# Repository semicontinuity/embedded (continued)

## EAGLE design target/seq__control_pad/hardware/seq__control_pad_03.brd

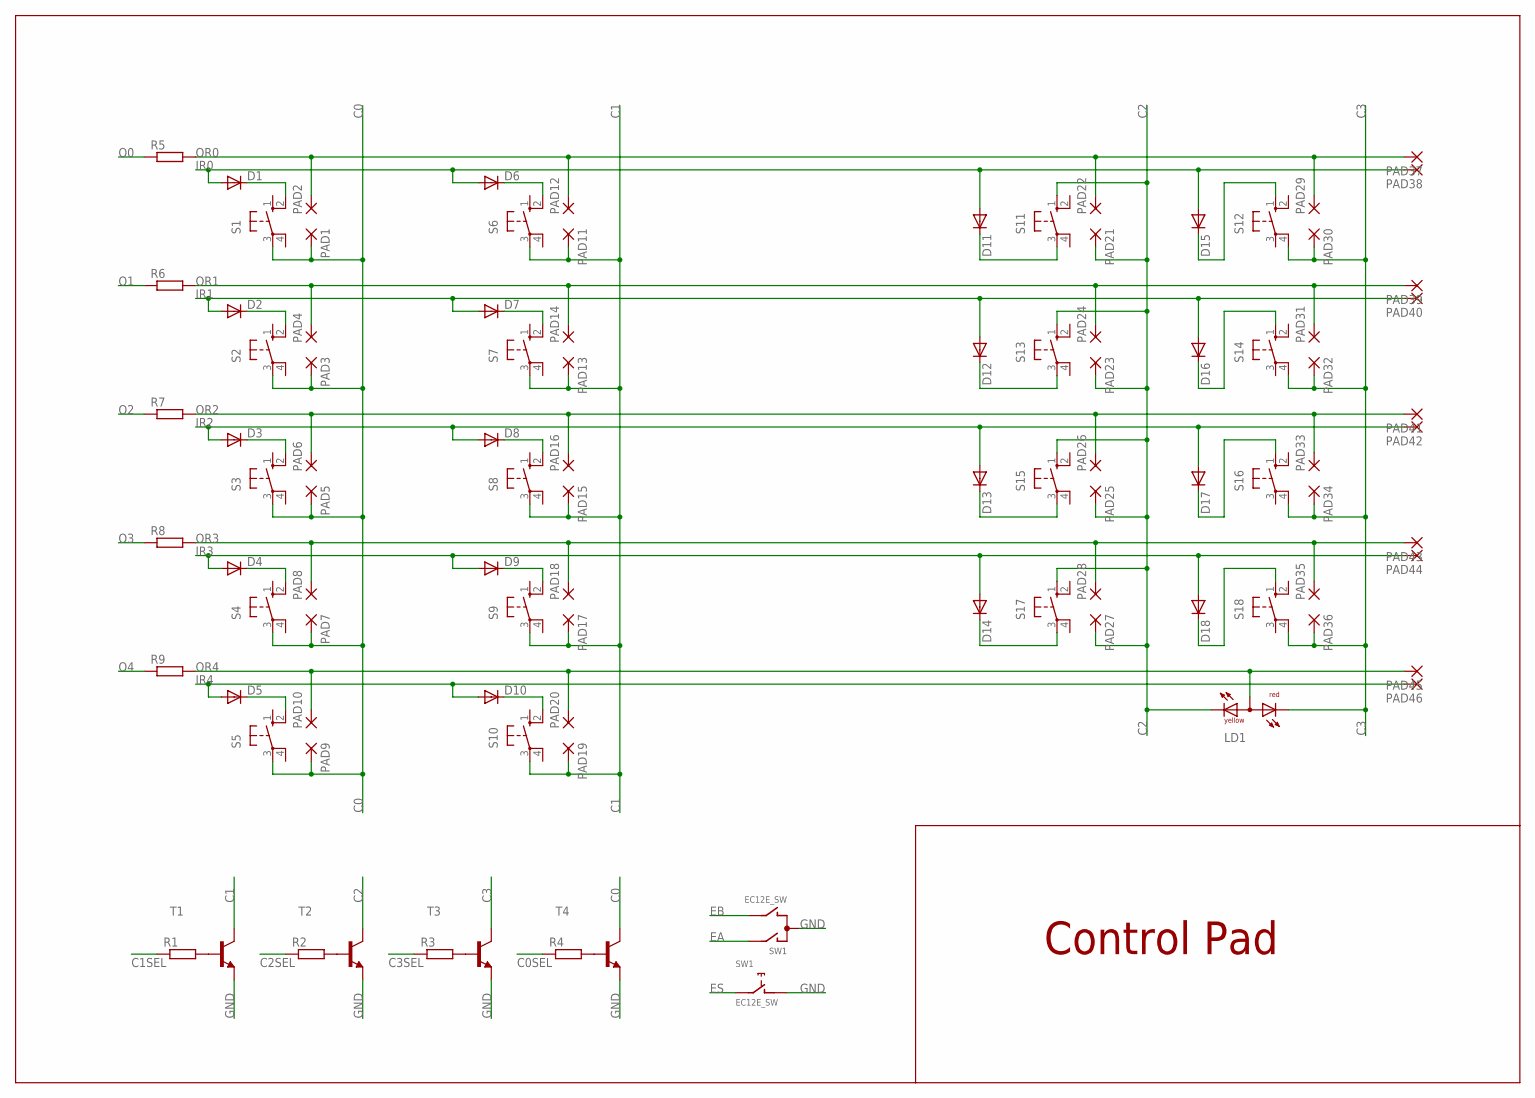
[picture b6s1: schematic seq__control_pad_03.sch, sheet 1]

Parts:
D1, D2, D3, D4, D5, D6, D7, D8, D9, D10, D11, D12, D13, D14, D15, D16, D17, D18: DIODE-MINIMELF; MINIMELF
LD1: DUOLED-RY-A; DUOLED-A-5MM
PAD1, PAD2, PAD3, PAD4, PAD5, PAD6, PAD7, PAD8, PAD9, PAD10, PAD11, PAD12, PAD13, PAD14, PAD15, PAD16, PAD17, PAD18, PAD19, PAD20, PAD21, PAD22, PAD23, PAD24, PAD25, PAD26, PAD27, PAD28, PAD29, PAD30, PAD31, PAD32, PAD33, PAD34, PAD35, PAD36, PAD37, PAD38, PAD39, PAD40, PAD41, PAD42, PAD43, PAD44, PAD45, PAD46: 1,6/0,8
R1, R2, R3, R4, R5, R6, R7, R8, R9: R-EU_R0805; R0805
S1, S2, S3, S4, S5, S6, S7, S8, S9, S10, S11, S12, S13, S14, S15, S16, S17, S18: 40-XX; B3F-40XX
SW1: EC12E_SW; ALPS_EC12E_SW
T1, T2, T3, T4: MMBT3904LT1-NPN-SOT23-BEC; SOT23-BEC

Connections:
C0: PAD1.1, PAD3.1, PAD5.1, PAD7.1, PAD9.1, S1.3, S2.3, S3.3, S4.3, S5.3, T4.C
C0SEL: R4.1; also elsewhere on the board
C1: PAD11.1, PAD13.1, PAD15.1, PAD17.1, PAD19.1, S6.3, S7.3, S8.3, S9.3, S10.3, T1.C
C1SEL: R1.1; also elsewhere on the board
C2: LD1.CX (CY), PAD21.1, PAD23.1, PAD25.1, PAD27.1, S11.1 (S), S13.1 (S), S15.1 (S), S17.1 (S), T2.C
C2SEL: R2.1; also elsewhere on the board
C3: LD1.CR, PAD30.1, PAD32.1, PAD34.1, PAD36.1, S12.4 (P1), S14.4 (P1), S16.4 (P1), S18.4 (P1), T3.C
C3SEL: R3.1; also elsewhere on the board
EA: SW1.A; also elsewhere on the board
EB: SW1.B; also elsewhere on the board
ES: SW1.E (2); also elsewhere on the board
GND: SW1.C, SW1.D (1), T1.E, T2.E, T3.E, T4.E; also elsewhere on the board
IR0: D1.A, D6.A, D11.A, D15.A, PAD38.1; also elsewhere on the board
IR1: D2.A, D7.A, D12.A, D16.A, PAD40.1; also elsewhere on the board
IR2: D3.A, D8.A, D13.A, D17.A, PAD42.1; also elsewhere on the board
IR3: D4.A, D9.A, D14.A, D18.A, PAD44.1; also elsewhere on the board
IR4: D5.A, D10.A, PAD46.1; also elsewhere on the board
unnamed: D11.C, S11.3
unnamed: R1.2, T1.B
unnamed: R2.2, T2.B
unnamed: R3.2, T3.B
unnamed: D3.C, S3.2 (S1)
unnamed: D16.C, S14.1 (S)
unnamed: R4.2, T4.B
unnamed: D17.C, S16.1 (S)
unnamed: D18.C, S18.1 (S)
unnamed: D1.C, S1.2 (S1)
unnamed: D2.C, S2.2 (S1)
unnamed: D5.C, S5.2 (S1)
unnamed: D4.C, S4.2 (S1)
unnamed: D6.C, S6.2 (S1)
unnamed: D7.C, S7.2 (S1)
unnamed: D8.C, S8.2 (S1)
unnamed: D9.C, S9.2 (S1)
unnamed: D10.C, S10.2 (S1)
unnamed: D12.C, S13.3
unnamed: D13.C, S15.3
unnamed: D14.C, S17.3
unnamed: D15.C, S12.1 (S)
O0: R5.1; also elsewhere on the board
O1: R6.1; also elsewhere on the board
O2: R7.1; also elsewhere on the board
O3: R8.1; also elsewhere on the board
O4: R9.1; also elsewhere on the board
OR0: PAD2.1, PAD12.1, PAD22.1, PAD29.1, PAD37.1, R5.2
OR1: PAD4.1, PAD14.1, PAD24.1, PAD31.1, PAD39.1, R6.2
OR2: PAD6.1, PAD16.1, PAD26.1, PAD33.1, PAD41.1, R7.2
OR3: PAD8.1, PAD18.1, PAD28.1, PAD35.1, PAD43.1, R8.2
OR4: LD1.A, PAD10.1, PAD20.1, PAD45.1, R9.2

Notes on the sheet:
Control Pad

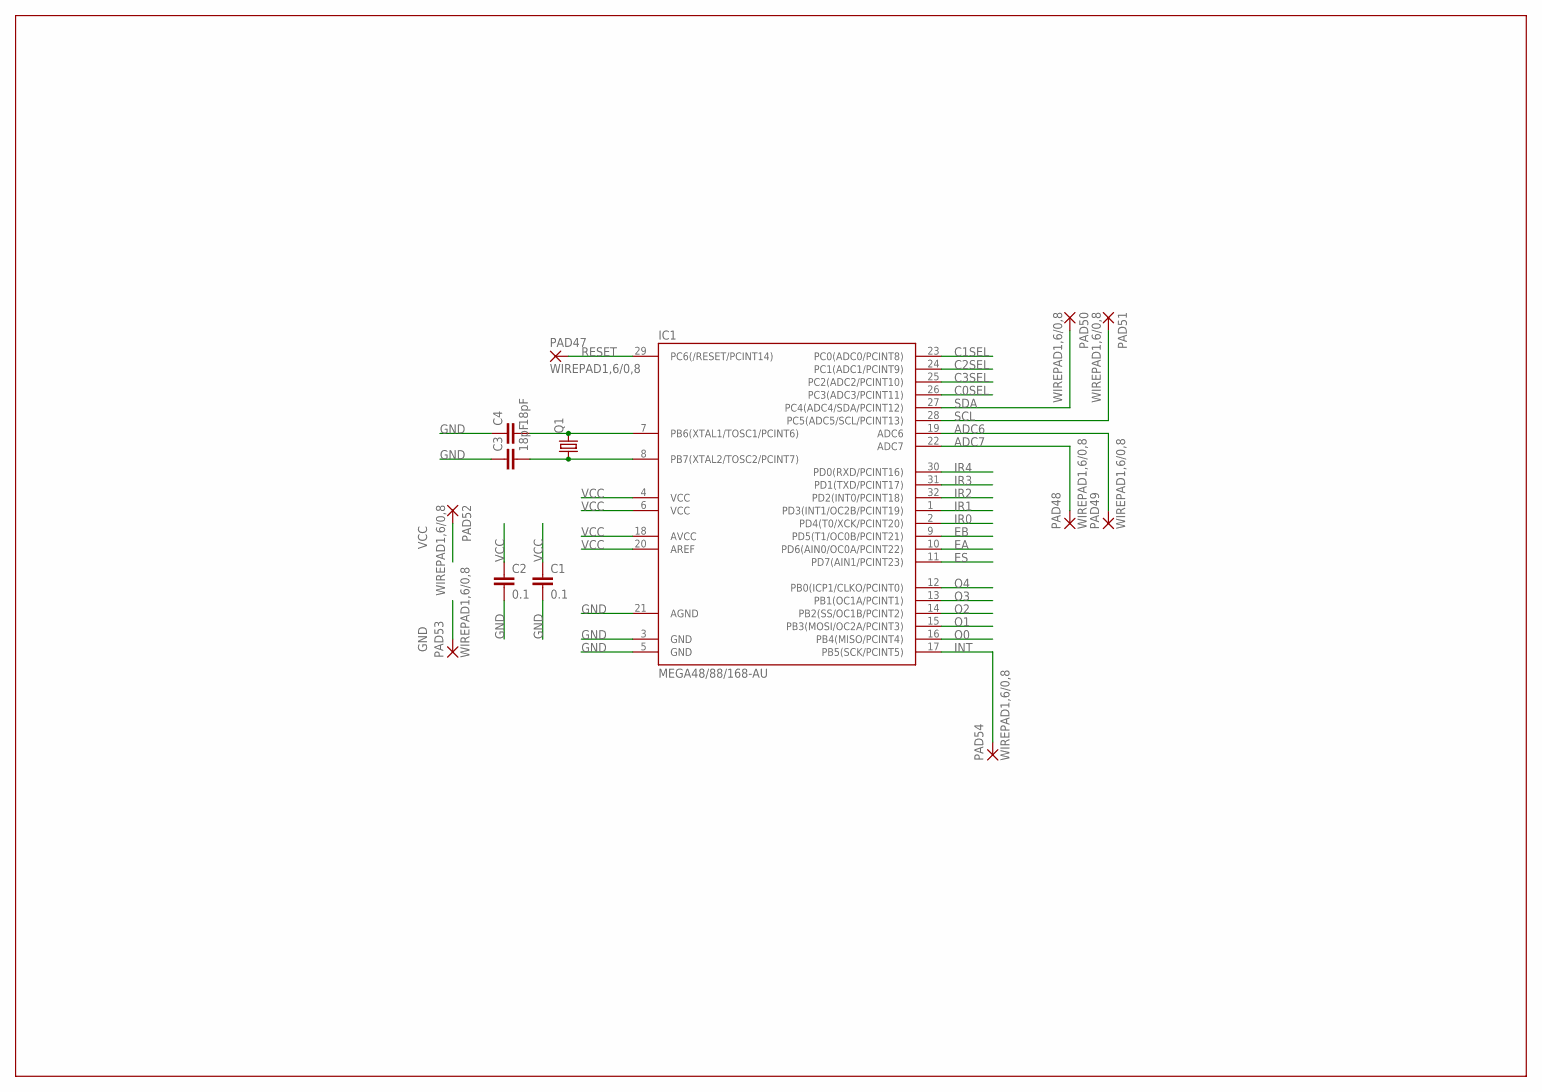
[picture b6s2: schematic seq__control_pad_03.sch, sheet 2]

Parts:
C1, C2: 0.1; C0805
C3, C4: 18pF; C0805
IC1: MEGA48/88/168-AU; TQFP32-08
PAD47, PAD48, PAD49, PAD50, PAD51, PAD52, PAD53, PAD54: WIREPAD1,6/0,8; 1,6/0,8
Q1: CRYSTALHC49S; HC49/S

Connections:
ADC6: IC1.19 (ADC6), PAD49.1
ADC7: IC1.22 (ADC7), PAD48.1
C0SEL: IC1.26 (PC3(ADC3/PCINT11)); also elsewhere on the board
C1SEL: IC1.23 (PC0(ADC0/PCINT8)); also elsewhere on the board
C2SEL: IC1.24 (PC1(ADC1/PCINT9)); also elsewhere on the board
C3SEL: IC1.25 (PC2(ADC2/PCINT10)); also elsewhere on the board
EA: IC1.10 (PD6(AIN0/OC0A/PCINT22)); also elsewhere on the board
EB: IC1.9 (PD5(T1/OC0B/PCINT21)); also elsewhere on the board
ES: IC1.11 (PD7(AIN1/PCINT23)); also elsewhere on the board
GND: C1.2, C2.2, C3.1, C4.1, IC1.3 (GND), IC1.5 (GND), IC1.21 (AGND), PAD53.1; also elsewhere on the board
INT: IC1.17 (PB5(SCK/PCINT5)), PAD54.1
IR0: IC1.2 (PD4(T0/XCK/PCINT20)); also elsewhere on the board
IR1: IC1.1 (PD3(INT1/OC2B/PCINT19)); also elsewhere on the board
IR2: IC1.32 (PD2(INT0/PCINT18)); also elsewhere on the board
IR3: IC1.31 (PD1(TXD/PCINT17)); also elsewhere on the board
IR4: IC1.30 (PD0(RXD/PCINT16)); also elsewhere on the board
O0: IC1.16 (PB4(MISO/PCINT4)); also elsewhere on the board
O1: IC1.15 (PB3(MOSI/OC2A/PCINT3)); also elsewhere on the board
O2: IC1.14 (PB2(SS/OC1B/PCINT2)); also elsewhere on the board
O3: IC1.13 (PB1(OC1A/PCINT1)); also elsewhere on the board
O4: IC1.12 (PB0(ICP1/CLKO/PCINT0)); also elsewhere on the board
RESET: IC1.29 (PC6(/RESET/PCINT14)), PAD47.1
SCL: IC1.28 (PC5(ADC5/SCL/PCINT13)), PAD51.1
SDA: IC1.27 (PC4(ADC4/SDA/PCINT12)), PAD50.1
VCC: C1.1, C2.1, IC1.4 (VCC), IC1.6 (VCC), IC1.18 (AVCC), IC1.20 (AREF), PAD52.1
XTAL1: C4.2, IC1.7 (PB6(XTAL1/TOSC1/PCINT6)), Q1.2
XTAL2: C3.2, IC1.8 (PB7(XTAL2/TOSC2/PCINT7)), Q1.1

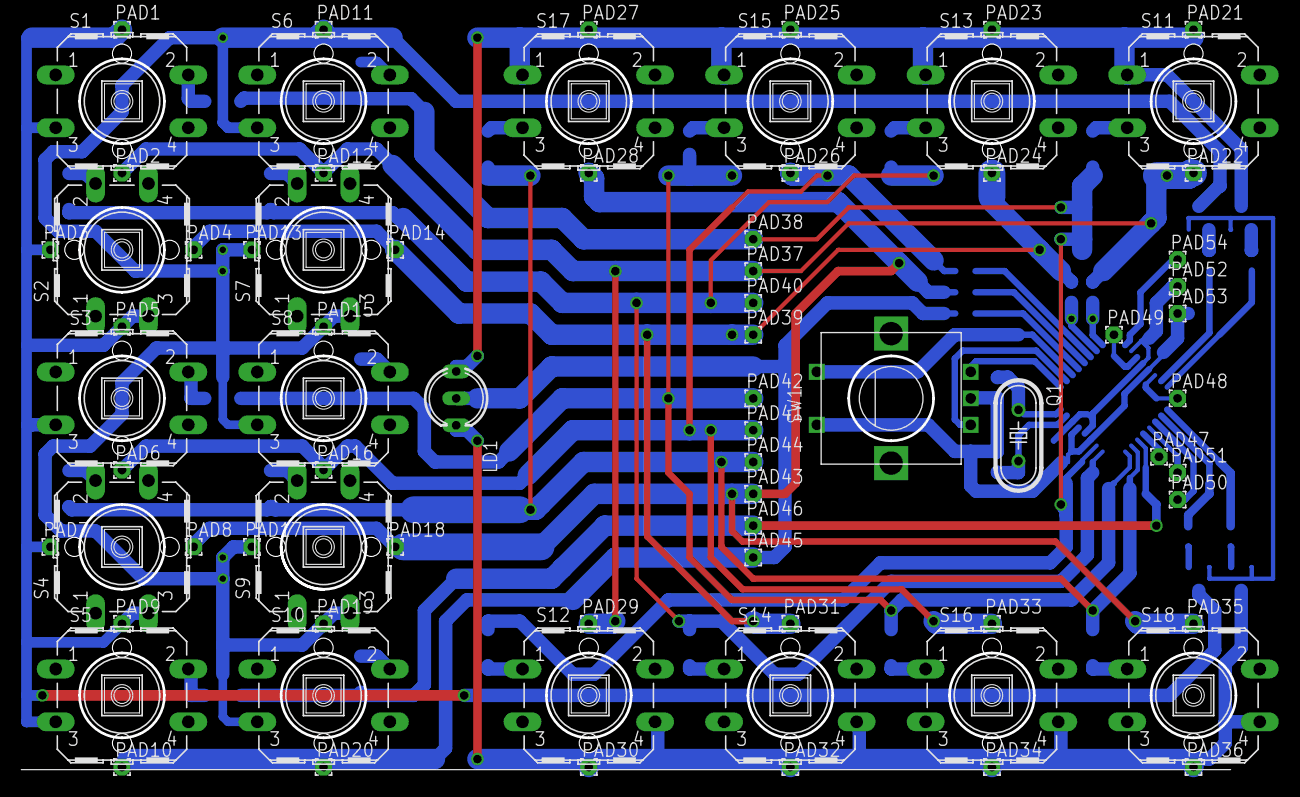
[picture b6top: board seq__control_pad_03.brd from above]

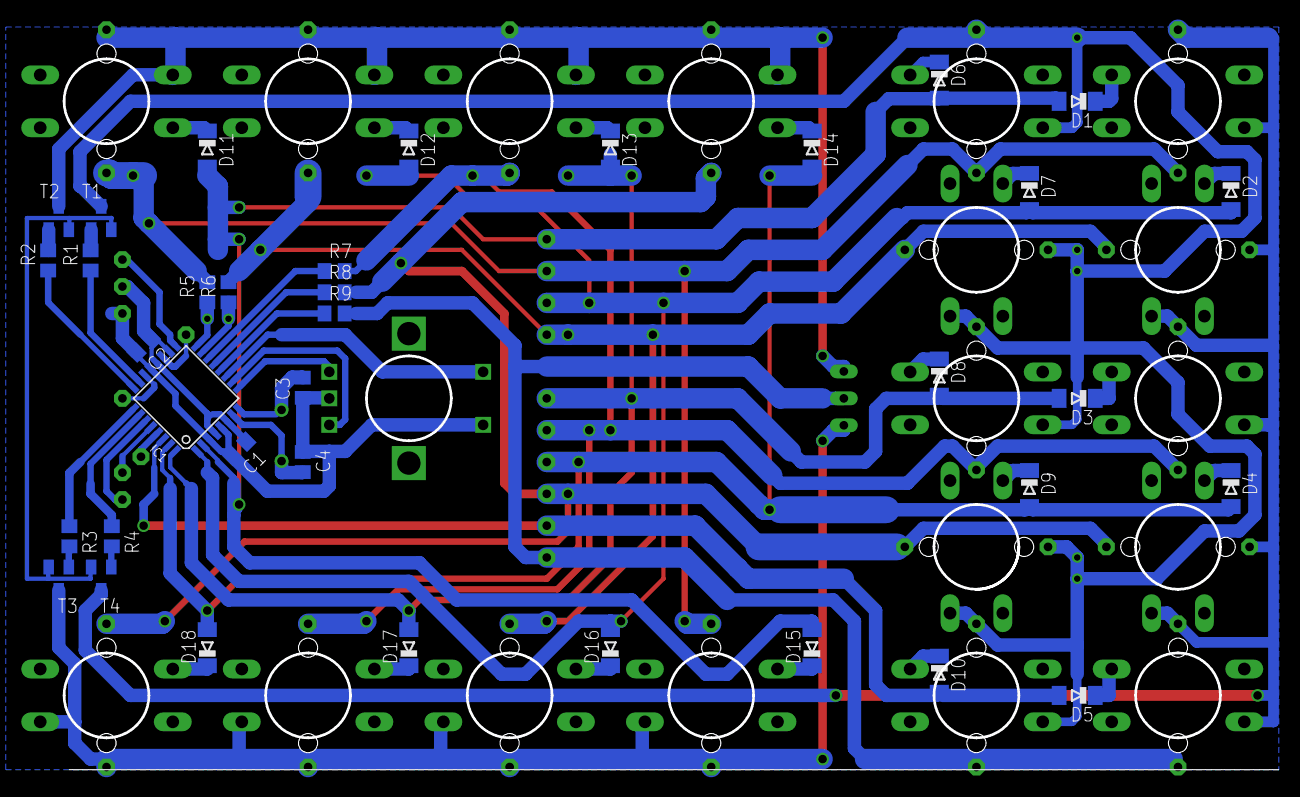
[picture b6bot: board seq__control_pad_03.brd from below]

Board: 2 copper layers, 114.5 x 67.0 mm, 111 parts (36 on the bottom side), 58 nets.

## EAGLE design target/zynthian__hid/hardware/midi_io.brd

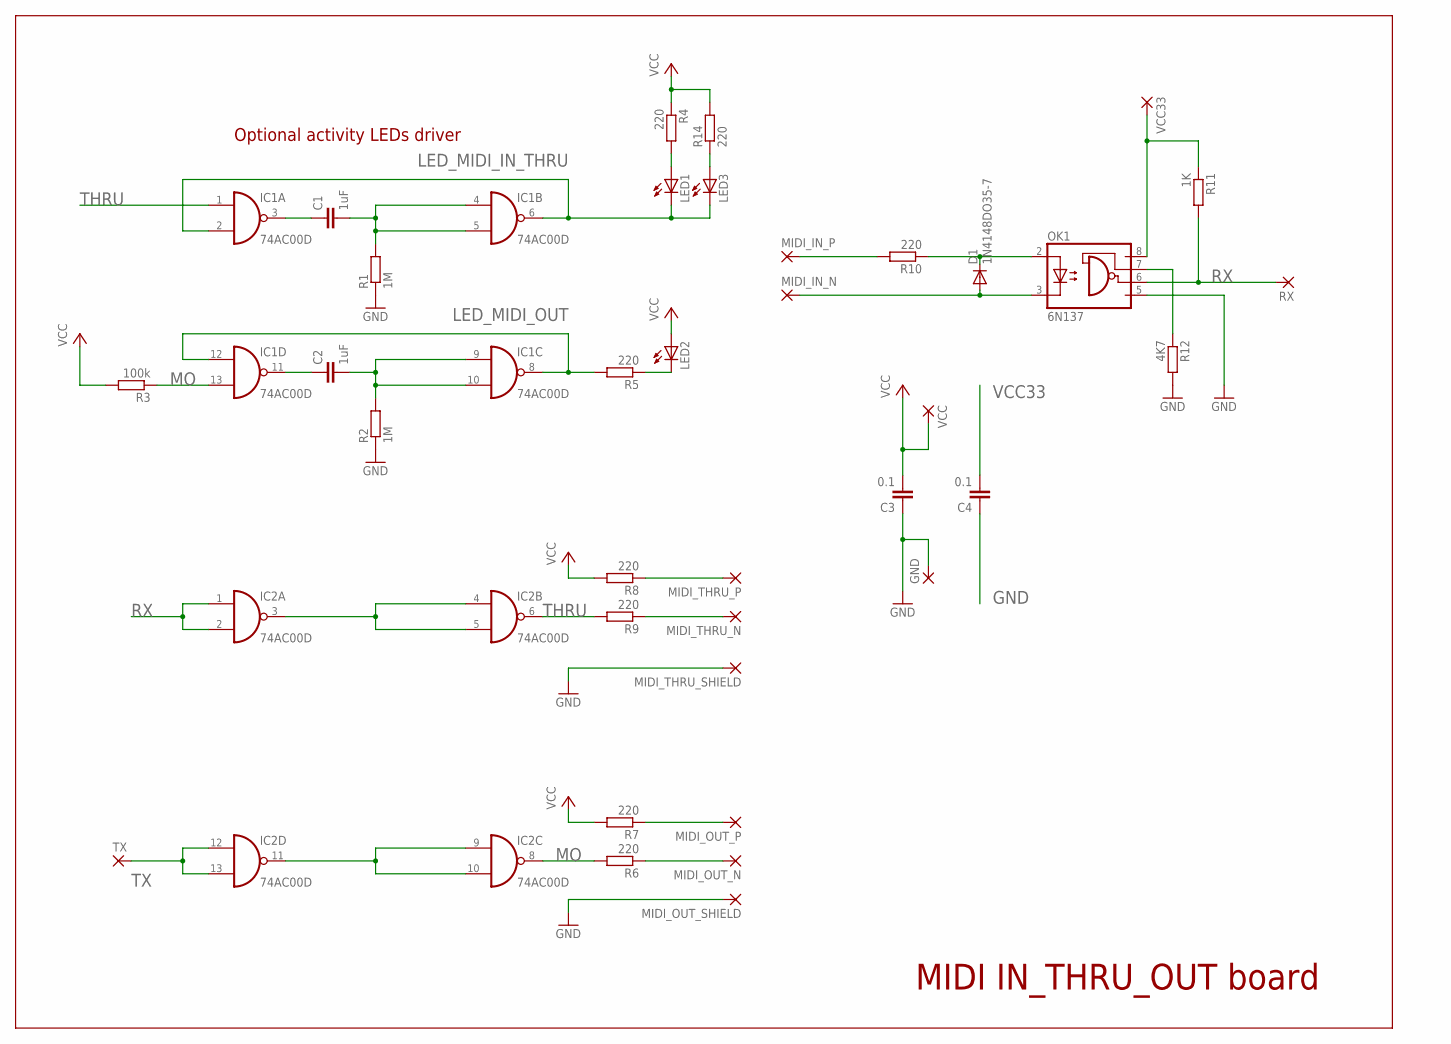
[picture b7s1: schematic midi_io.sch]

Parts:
C1, C2: 1uF; C0805
C3, C4: 0.1; C0805
D1: 1N4148DO35-7; DO35-7
GND: 1,6/0,8
IC1, IC2: 74AC00D; SO14
LED1, LED2, LED3: LED3MM
MIDI_IN_N: 1,6/0,8
MIDI_IN_P: 1,6/0,8
MIDI_OUT_N: 1,6/0,8
MIDI_OUT_P: 1,6/0,8
MIDI_OUT_SHIELD: 1,6/0,8
MIDI_THRU_N: 1,6/0,8
MIDI_THRU_P: 1,6/0,8
MIDI_THRU_SHIELD: 1,6/0,8
OK1: 6N137; DIL08
R1, R2: 1M; M0805
R3: 100k; M0805
R4, R6, R7, R8, R9, R10: 220; 0204/7
R5: 220; M0805
R11: 1K; 0204/7
R12: 4K7; 0204/7
R14: 220; 0617/17
RX: 1,6/0,8
TX: 1,6/0,8
VCC, VCC33: 1,6/0,8

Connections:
GND: C3.1, C4.1, GND.1, IC1.7 (GND), IC2.7 (GND), MIDI_OUT_SHIELD.1, MIDI_THRU_SHIELD.1, OK1.5 (GND), R1.1, R2.1, R12.2
INV1: IC2.3 (O), IC2.4 (I0), IC2.5 (I1)
INV2: IC2.9 (I0), IC2.10 (I1), IC2.11 (O)
L2: LED2.K (C), R5.1
LED_MIDI_IN_THRU: IC1.2 (I1), IC1.6 (O), LED1.K (C), LED3.K (C)
LED_MIDI_OUT: IC1.8 (O), IC1.12 (I0), R5.2
MIDI_THRU_N: MIDI_THRU_N.1, R9.1
MIDI_THRU_P: MIDI_THRU_P.1, R8.1
MIDI_TX_N: MIDI_OUT_N.1, R6.1
MIDI_TX_P: MIDI_OUT_P.1, R7.1
MO: IC1.13 (I1), IC2.8 (O), R3.1, R6.2
unnamed: OK1.7 (VE), R12.1
unnamed: LED1.A, R4.2
unnamed: LED3.A, R14.1
unnamed: D1.C, OK1.2 (A), R10.1
unnamed: D1.A, MIDI_IN_N.1, OK1.3 (C)
unnamed: MIDI_IN_P.1, R10.2
RC1: C1.2, IC1.4 (I0), IC1.5 (I1), R1.2
RC2: C2.2, IC1.9 (I0), IC1.10 (I1), R2.2
RX: IC2.1 (I0), IC2.2 (I1), OK1.6 (VO), R11.2, RX.1
THRU: IC1.1 (I0), IC2.6 (O), R9.2
TO_C1: C1.1, IC1.3 (O)
TO_C2: C2.1, IC1.11 (O)
TX: IC2.12 (I0), IC2.13 (I1), TX.1
VCC: C3.2, IC1.14 (VCC), IC2.14 (VCC), LED2.A, R3.2, R4.1, R7.2, R8.2, R14.2, VCC.1
VCC33: C4.2, OK1.8 (VCC), R11.1, VCC33.1

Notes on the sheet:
Optional activity LEDs driver
MIDI IN_THRU_OUT board

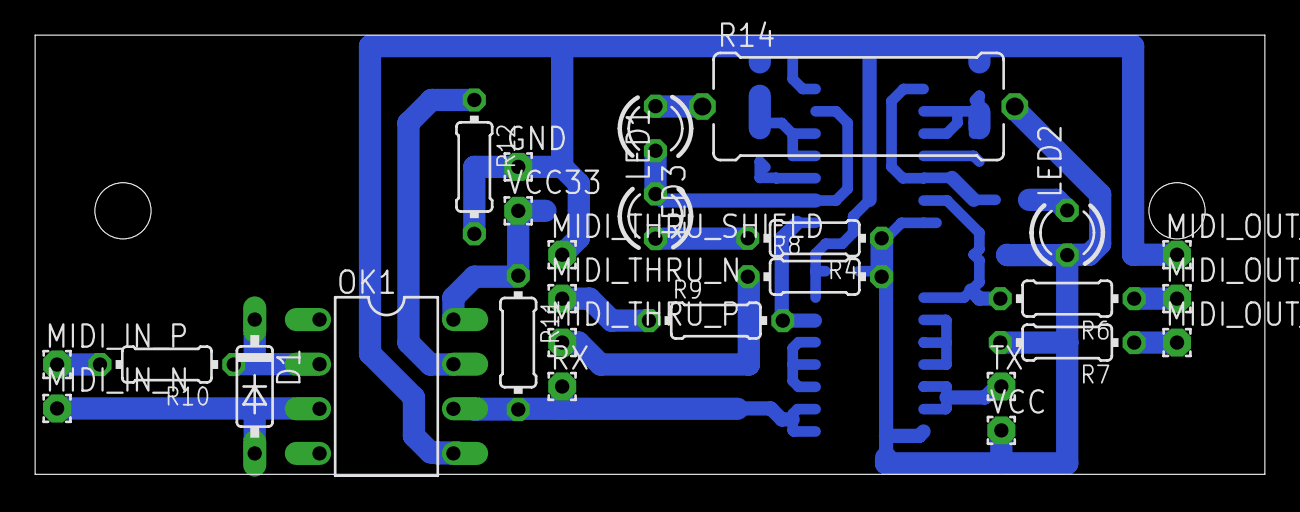
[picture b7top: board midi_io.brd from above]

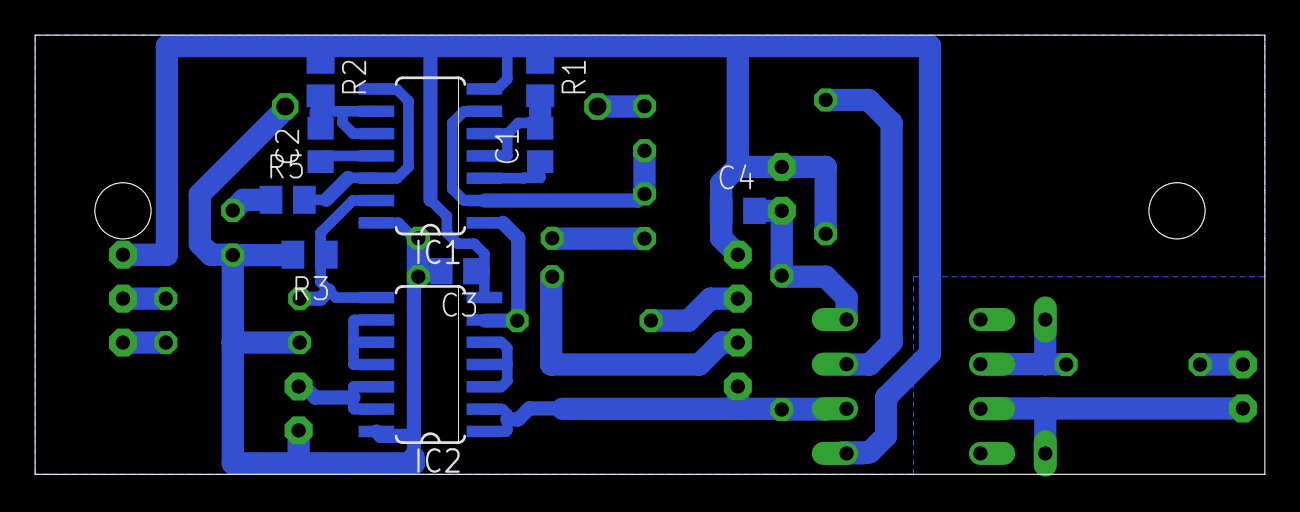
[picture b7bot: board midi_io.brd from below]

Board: 2 copper layers, 70.0 x 25.0 mm, 37 parts (10 on the bottom side), 26 nets.

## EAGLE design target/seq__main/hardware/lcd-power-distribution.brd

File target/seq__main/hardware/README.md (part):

## General information

Pins that are not 5V tolerant:

- PA4
- PA5

Pins than can only sink 3mA max:

- PC13
- PC14
- PC15

## SPI pin-out

|                 |      | Conflict         |
|-----------------|------|------------------|
| SPI1_NSS        | PA4  |                  |
| SPI3_NSS        | PA4  |                  |
| SPI1_SCK        | PA5  |                  |
| SPI1_MISO       | PA6  |                  |
| SPI1_MOSI       | PA7  | ETH_RMII_CRS_DV  |
| SPI1_NSS        | PA15 |                  |
| SPI3_NSS        | PA15 |                  |
| SPI1_SCK        | PB3  | DIS1_D3          |
| SPI3_SCK        | PB3  | DIS1_D3          |
| SPI1_MISO       | PB4  | DIS1_D4          |
| SPI3_MISO       | PB4  | DIS1_D4          |
| SPI1_MOSI       | PB5  | DIS1_D5          |
| SPI3_MOSI       | PB5  | DIS1_D5          |
| SPI2_NSS        | PB9  | I2C1_SDA         |
| SPI2_SCK        | PB10 |                 +|
| SPI2_NSS        | PB12 | ETH_RMII_TXD0    |
| SPI2_SCK        | PB13 | ETH_RMII_TXD1    |
| SPI2_MISO       | PB14 |                  |
| SPI2_MOSI       | PB15 |                  |
| SPI2_MISO       | PC2  |                 +|
| SPI2_MOSI       | PC3  |                 +|
| SPI3_SCK        | PC10 | SDIO_D2          |
| SPI3_MISO       | PC11 | SDIO_D3          |
| SPI3_MOSI       | PC12 | SDIO_CK          |

## I2C pin-out

|                 |      | Conflict         |
|-----------------|------|------------------|
| I2C3_SCL        | PA8  |                  |
| I2C3_SMBA       | PA9  |                  |
| I2C1_SMBA       | PB5  |                  |
| I2C1_SCL        | PB6  |                  |
| I2C1_SDA        | PB7  |                  |
| I2C1_SCL        | PB8  |                  |
| I2C1_SDA        | PB9  |                  |
| I2C2_SCL        | PB10 |                  |
| I2C2_SDA        | PB11 | ETH_RMII_TX_EN   | 
| I2C2_SMBA       | PB12 | ETH_RMII_TXD0    |
| I2C3_SDA        | PC9  | SDIO_D1          |

## USART pin-out

|                 |      | Conflict         |
|-----------------|------|------------------|
| UART4_TX        | PA0  | TX ONLY        ? |
| UART4_RX        | PA1  | ETH_RMII_REF_CLK |
| USART2_TX       | PA2  | ETH_MDIO         |
| USART2_RX       | PA3  | DIS3_RW?         |
| USART1_TX       | PA9  | OTG_FS_VBUS    ? |
| USART1_RX       | PA10 | OTG_FS_ID      ? |
| USART1_TX       | PB6  | DIS1_D6          |
| USART1_RX       | PB7  | DIS1_D7          |
| USART3_TX       | PB10 | SPI2_SCK?        |
| USART3_RX       | PB11 | ETH_RMII_TX_EN   |
| USART6_TX       | PC6  | SPI CS? (OK?)    |
| USART6_RX       | PC7  | SPI CS? (OK?)    |
| USART3_TX       | PC10 | SDIO_D2          |
| USART3_RX       | PC11 | SDIO_D3          |
| UART4_TX        | PC10 | SDIO_D2          |
| UART4_RX        | PC11 | SDIO_D3          |
| UART5_TX        | PC12 | SDIO_CK          |
| UART5_RX        | PD2  | SDIO_CMD         |
| USART2_TX       | PD5  | +                |
| USART2_RX       | PD6  | +                |
| USART3_TX       | PD8  | DIS0_D0          |
| USART3_RX       | PD9  | DIS0_D1          |

## SD Card slot pin-out (9; 1-8)

|    |         |
|----|---------|
|  1 | CD/DAT3 |
|  2 | CMD     |
|  3 | Vss1    |
|  4 | Vdd     |
|  5 | CLK     |
|  6 | Vss2    |
|  7 | DAT0    |
|  8 | DAT1    |
|  9 | DAT2    |

## SD Card connections

|    |        |
|----|--------|
|PC8 |SDIO_D0 |
|PC9 |SDIO_D1 |
|PC10|SDIO_D2 |
|PC11|SDIO_D3 |
|PC12|SDIO_CK |
|PD2 |SDIO_CMD|

## Ethernet PHY connections

|                 |      |
|-----------------|------|
|ETH_RMII_REF_CLK | PA1  |
|ETH_MDIO         | PA2  |
|ETH_RMII_CRS_DV  | PA7  |
|ETH_MDC          | PC1  |
|ETH_RMII_RXD0    | PC4  |
|ETH_RMII_RXD1    | PC5  |
|ETH_RMII_TX_EN   | PB11 |
|ETH_RMII_TXD0    | PB12 |
|ETH_RMII_TXD1    | PB13 |
|ETH_RST_PIN (OPT)| PE2  |

## USB OTG FS connections

|                 |      |
|-----------------|------|
|OTG_FS_SOF       | PA8  |
|OTG_FS_VBUS      | PA9  |
|OTG_FS_ID        | PA10 |
|OTG_FS_DM        | PA11 |
|OTG_FS_DP        | PA12 |

## CAN connections

|                 |      |
|-----------------|------|
|CAN1_RX          | PA11 |
|CAN1_TX          | PA12 |
|CAN2_RX          | PB5  |
|CAN2_TX          | PB6  |
|CAN1_RX          | PB8  |
|CAN1_TX          | PB9  |
|CAN2_RX          | PB12 |
|CAN2_TX          | PB13 |
|CAN1_RX          | PD0  |
|CAN1_TX          | PD1  |

## DIY More board pin-out (bottom view, outdated)

|            |    |    |            |    |    |    |    |    |    |    |    |    |    |    |    |            |    |    |            |
|------------|----|----|------------|----|----|----|----|----|----|----|----|----|----|----|----|------------|----|----|------------|
|            |    |    |            |    |DIS3|DIS3|ETH |ETH |    |    |    |    |    |    |SDIO|            |    |    |            |
|            |    |    |            |    |D5  |D7  |RMII|RMII|    |    |    |    |    |    |D0  |            |    |    |            |
|            |    |    |            |    |    |    |TXEN|TXD0|    |    |    |    |    |    |    |            |    |    |            |
|------------|----|----|------------|----|----|----|----|----|----|----|----|----|----|----|----|------------|----|----|------------|
|            |    |    |            |PE11|PE13|PE15|PB11|PB12|PB14|PD8 |PD10|PD12|PD14|PC6 |PC8 |            |    |    |            |
|            |    |    |            |PE12|PE14|PB10|GND |3.3V|PB13|PB15|PD9 |PD11|PD13|PD15|PC7 |            |    |    |            |
|------------|----|----|------------|----|----|----|----|----|----|----|----|----|----|----|----|------------|----|----|------------|
|            |    |    |            |DIS3|DIS3|    |    |    |ETH |    |    |    |    |    |    |            |    |    |            |
|            |    |    |            |D4  |D6  |    |    |    |RMII|    |    |    |    |    |    |            |    |    |            |
|            |    |    |            |    |    |    |    |    |TXD1|    |    |    |    |    |    |            |    |    |            |
|------------|----|----|------------|----|----|----|----|----|----|----|----|----|----|----|----|------------|----|----|------------|
|            |GND |BT1 |            |    |    |    |    |    |    |    |    |    |    |    |    |            |    |    |            |
|            |GND |BT0 |            |    |    |    |    |    |    |    |    |    |    |    |    |            |    |    |            |
|            |PB2 |PE10|DIS3_D2     |    |    |    |    |    |    |    |    |    |    |    |    |            |VCC |GND |            |
|DIS3_D1     |PE9 |PE8 |DIS3_D0     |    |    |    |    |    |    |    |    |    |    |    |    |SDIO_D1     |PC9 |PA8 |            |
|            |PE7 |PE1 |            |    |    |    |    |    |    |    |    |    |    |    |    |            |PA9 |PA10|            |
|            |PB9 |PB8 |            |    |    |    |    |    |    |    |    |    |    |    |    |            |PA11|PA12|            |
|            |PB1 |PB0 |            |    |    |    |    |    |    |    |    |    |    |    |    |            |PA13|PA14|            |
|ETR1        |PC5 |PC4 |ETR0        |    |    |    |    |    |    |    |    |    |    |    |    |            |PA15|PC10|SDIO_D2     |
|ETDV        |PA7 |PA6 |            |    |    |    |    |    |    |    |    |    |    |    |    |SDIO_D3     |PC11|PC12|SDIO_CK     |
|            |PA5 |PA4 |            | -- | -- |    |    |    |    |    |    |    |    |    |    |            |PD0 |PD1 |            |
|            |PA3 |PC3 |            |    |    |    |    |    |    |    |    |    |    |    |    |SDIO_CMD    |PD2 |PD3 |            |
|ETMI        |PA2 |PA1 |ETH_REF_CLK |    |    |    |    |    |    |    |    |    |    |    |    |            |PD4 |PD5 |            |
|            |PA0 |PC2 |            |    |    |    |    |    |    |    |    |    |    |    |    |            |PD6 |PD7 |            |
|ETMC        |PC1 |PC0 |            |    |    |    |    |    |    |    |    |    |    |    |    |            |PB3 |PB4 |            |
|            |GND |3.3V|            |    |    |    |    |    |    |    |    |    |    |    |    |            |PB5 |PB6 |            |
|            |PC13|PE6 |            | -- |    |    |    |    |    |    |    |    |    |    |    |            |PB7 |PE0 |DIS2_D0     |
|            |PE5 |PE4 |            |    |    |    |    |    |    |    |    |    |    |    |    |            |3.3V|GND |            |
|            |PE3 |PE2 |            |    |    |    |    |    |    |    |    |    |    |    |    |            |VCC |GND |            |

## DIY More board pin-out (top view)

|            |    |    |            |    |    |    |    |    |    |    |    |    |    |    |    |            |    |    |            |
|------------|----|----|------------|----|----|----|----|----|----|----|----|----|----|----|----|------------|----|----|------------|
|            |    |    |            |SDIO|?SPI|DIS0|DIS0|DIS0|DIS0|?SPI|ETH |ETH |DIS3|DIS3|DIS3|            |    |    |            |
|            |    |    |            |D0  |CS1 |D6  |D4  |D2  |D0  |MISO|TXD0|TX  |D7  |D5  |D3  |            |    |    |            |
|            |    |    |            |    |    |    |    |    |    |    |&   |EN  |    |    |    |            |    |    |            |
|------------|----|----|------------|----|----|----|----|----|----|----|----|----|----|----|----|------------|----|----|------------|
|            |    |    |            |PC8 |PC6 |PD14|PD12|PD10|PD8 |PB14|PB12|PB11|PE15|PE13|PE11|            |    |    |            |
|            |    |    |            |PC7 |PD15|PD13|PD11|PD9 |PB15|PB13|3.3V|GND |PB10|PE14|PE12|            |    |    |            |
|------------|----|----|------------|----|----|----|----|----|----|----|----|----|----|----|----|------------|----|----|------------|
|            |    |    |            |?SPI|DIS0|DIS0|DIS0|DIS0|?SPI|ETH |3.3V|GND |?SPI|DIS3|DIS3|            |    |    |            |
|            |    |    |            |CS2 |D7  |D5  |D3  |D1  |MOSI|TXD1|    |    |SCK |D6  |D4  |            |    |    |            |
|            |    |    |            |    |    |    |    |    |    |&   |    |    |    |    |    |            |    |    |            |
|------------|----|----|------------|----|----|----|----|----|----|----|----|----|----|----|----|------------|----|----|------------|
|            |    |    |            |    |    |    |    |    |    |    |    |    |    |    |    |BOOT1       |BT1 |GND |GND         |
|            |    |    |            |    |    |    |    |    |    |    |    |    |    |    |    |BOOT0       |BT0 |GND |GND         |
|GND         |GND |VCC |VCC         |    |    |    |    |    |    |    |    |    |    |    |    |DIS3_D2     |PE10|PB2 |DIS1_D2     |
|OTG_FS_SOF  |PA8 |PC9 |SDIO_D1     |    |    |    |    |    |    |    |    |    |    |    |    |DIS3_D0     |PE8 |PE9 |DIS3_D1     |
|OTG_FS_ID   |PA10|PA9 |OTG_FS_VBUS |    |    |    |    |    |    |    |    |    |    |    |    |DIS2_D1     |PE1 |PE7 |DIS2_D7     |
|OTF_FS_DP   |PA12|PA11|OTG_FS_DM   |    |    |    |    |    |    |    |    |    |    |    |    |I2C1_SCL  & |PB8 |PB9 |I2C1_SDA  & |
|DIS1_RW     |PA14|PA13|DIS1_RS     |    |    |    |    |    |    |    |    |    |    |    |    |DIS1_D0     |PB0 |PB1 |DIS1_D1     |
|SDIO_D2     |PC10|PA15|DIS1_E      |    |    |    |    |    |    |    |    |    |    |    |    |ETH_RXD0    |PC4 |PC5 |ETH_RXD1    |
|SDIO_CK     |PC12|PC11|SDIO_D3     |    |    |    |    |    |    |    |    |    |    |    |    |DIS3_E      |PA6 |PA7 |ETH_CRS_DV  |
|CAN1_TX?  & |PD1 |PD0 |CAN1_RX?  & |    |    |    |    |    |    |    |    |    |    | -- | -- |INT1?       |PA4 |PA5 |INT2?       |
|DIS0_E      |PD3 |PD2 |SDIO_CMD    |    |    |    |    |    |    |    |    |    |    |    |    |DIS2_E      |PC3 |PA3 |DIS3_RW     |
|USART2_TX   |PD5 |PD4 |DIS0_RS     |    |    |    |    |    |    |    |    |    |    |    |    |ETH_REF_CLK |PA1 |PA2 |ETH_MDIO    |
|DIS0_RW     |PD7 |PD6 |USART2_RX   |    |    |    |    |    |    |    |    |    |    |    |    |DIS2_RW     |PC2 |PA0 |PWM?        |
|DIS1_D4     |PB4 |PB3 |DIS1_D3     |    |    |    |    |    |    |    |    |    |    |    |    |DIS2_RS     |PC0 |PC1 |ETH_MDC     |
|DIS1_D6   & |PB6 |PB5 |DIS1_D5   & |    |    |    |    |    |    |    |    |    |    |    |    |3.3V        |3.3V|GND |GND         |
|DIS2_D0     |PE0 |PB7 |DIS1_D7     |    |    |    |    |    |    |    |    |    |    |    | -- |DIS2_D6     |PE6 |PC13|DIS3_RS     |
|GND         |GND |3.3V|3.3V        |    |    |    |    |    |    |    |    |    |    |    |    |DIS2_D4     |PE4 |PE5 |DIS2_D5     |
|GND         |GND |VCC |VCC         |    |    |    |    |    |    |    |    |    |    |    |    |DIS2_D2     |PE2 |PE3 |DIS2_D3     |

## Pin-outs by port

|    |                             |
|----|-----------------------------|
|PA0 | PWM?                        |
|PA1 | ETH_REF_CLK                 |
|PA2 | ETH_MDI                     |
|PA3 | DIS3_RW                     |
|PA4 | (not 5V tolerant)           |
|PA5 | (not 5V tolerant)           |
|PA6 | DIS3_E                      |
|PA7 | ETH_RMII_CRS_DV             |
|PA8 | OTG_FS_SOF                  |
|PA9 | OTG_FS_VBUS                 |
|PA10| OTG_FS_ID                   |
|PA11| OTF_FS_DM                   |
|PA12| OTG_FS_DP                   |
|PA13| DIS1_RS (+ SWD)             |
|PA14| DIS1_RW (+ SWD)             |
|PA15| DIS1_E                      |
|PB0 | DIS1_D0                     |
|PB1 | DIS1_D1                     |
|PB2 | DIS1_D2                     |
|PB3 | DIS1_D3 (+ SWO)             |
|PB4 | DIS1_D4                     |
|PB5 | DIS1_D5                     |
|PB6 | DIS1_D6                     |
|PB7 | DIS1_D7                     |
|PB8 | I2C1_SCL                    |
|PB9 | I2C1_SDA                    |
|PB10| SPI2_SCK (no NSS)?      SPI |
|PB11| ETH_RMII_TX_EN              |
|PB12| ETH_RMII_TXD0               |
|PB13| ETH_RMII_TXD1               |
|PB14| SPI2_MISO (no NSS)?         |
|PB15| SPI2_MOSI (no NSS)?         |
|PC0 | DIS2_RS                     |
|PC1 | ETH_MDC                     |
|PC2 | DIS2_RW                 SPI |
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
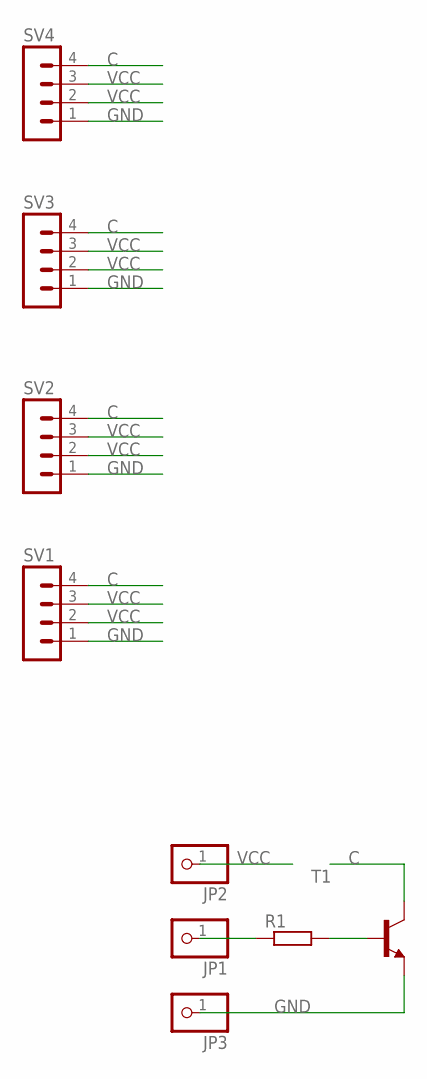
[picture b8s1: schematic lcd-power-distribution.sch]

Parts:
JP1, JP2, JP3: PINHD-1X1; 1X01
R1: R-EU_0207/7; 0207/7
SV1, SV2, SV3, SV4: MA04-1
T1: 2N3904-NPN-TO92-EBC; TO92-EBC

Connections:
C: SV1.4, SV2.4, SV3.4, SV4.4, T1.C
GND: JP3.1, SV1.1, SV2.1, SV3.1, SV4.1, T1.E
unnamed: JP1.1, R1.1
unnamed: R1.2, T1.B
VCC: JP2.1, SV1.2, SV1.3, SV2.2, SV2.3, SV3.2, SV3.3, SV4.2, SV4.3

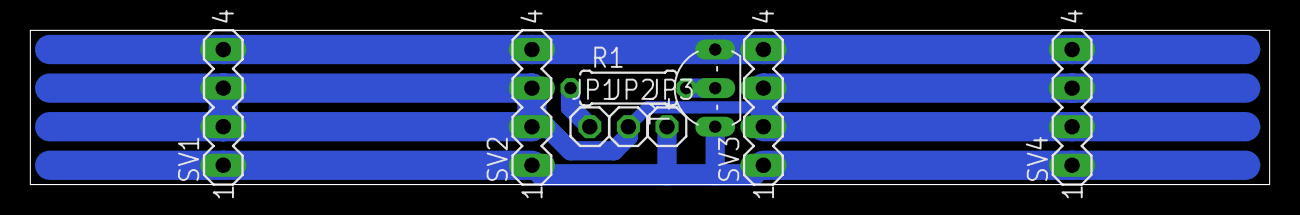
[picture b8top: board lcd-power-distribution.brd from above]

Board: 2 copper layers, 81.6 x 10.2 mm, 9 parts (0 on the bottom side), 5 nets.

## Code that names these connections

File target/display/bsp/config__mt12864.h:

#ifndef __MT12864_CONNECTION_H
#define __MT12864_CONNECTION_H


/*--------------------------------------------------------------------------------------------*/
/* LCD control lines are attached to port C                                                   */
/*--------------------------------------------------------------------------------------------*/

/*--------------------------------------------------------------------------------------------*/
/* Line E connected to PC0.                                                                   */
/* Active level - high                                                                        */
/*--------------------------------------------------------------------------------------------*/
#define   LCD_E               0

/*--------------------------------------------------------------------------------------------*/
/* Line A0 (data/command) is connected to PC1.                                                */
/* "1" - data transmission, "0" - command transmission.                                       */
/*--------------------------------------------------------------------------------------------*/
#define   LCD_A0              1

/*--------------------------------------------------------------------------------------------*/
/* Line RW (read/write) is connected to PC2.                                                  */
/* "1" - read cycle, "0" - write cycle.                                                       */
/*--------------------------------------------------------------------------------------------*/
#define   LCD_RW              2

/*--------------------------------------------------------------------------------------------*/
/* Line CS2 (select chip 2) is connected to PC3.                                              */
/* Active level - low                                                                         */
/*--------------------------------------------------------------------------------------------*/
#define   LCD_CS2             3

/*--------------------------------------------------------------------------------------------*/
/* Line CS1 (select chip 1) is connected to PC4.                                              */
/* Active level - low                                                                         */
/*--------------------------------------------------------------------------------------------*/
#define   LCD_CS1             4

/*--------------------------------------------------------------------------------------------*/
/* Line RES (reset) is connected to PC5.                                                      */
/* Active level - low                                                                         */
/*--------------------------------------------------------------------------------------------*/
#define   LCD_RES             5

/*--------------------------------------------------------------------------------------------*/
/* Backlight control is connected to PC6.                                                     */
/* "1" - backlight on, "0" - backlight off.                                                   */
/*--------------------------------------------------------------------------------------------*/
#define   LCD_BACKLIGHT         6





#define mt12864_clear_line(pin) cbi(PORTC, (pin))
//#define clear_lines_in_lcd_control_port(mask) PORTC &= ~(mask)
#define mt12864_set_line(pin) sbi(PORTC, (pin))
//#define set_lines_in_lcd_control_port(mask) PORTC |= (mask)

#define mt12864_is_line_set(pin) bit_is_set(PINC, (pin))


#define mt12864_clear_line_E   mt12864_clear_line(LCD_E)
#define mt12864_clear_line_RW  mt12864_clear_line(LCD_RW)
#define mt12864_clear_line_A0  mt12864_clear_line(LCD_A0)
#define mt12864_clear_line_RES mt12864_clear_line(LCD_RES)
#define mt12864_set_line_E     mt12864_set_line(LCD_E)
#define mt12864_set_line_RW    mt12864_set_line(LCD_RW)
#define mt12864_set_line_A0    mt12864_set_line(LCD_A0)
#define mt12864_set_line_RES   mt12864_set_line(LCD_RES)


// This ternary construct is more efficient - compiles to 10 bytes
#define mt12864_clear_cs(chip) (chip == 0) ? (mt12864_clear_line(LCD_CS1)) : (mt12864_clear_line(LCD_CS2))
#define mt12864_set_cs {mt12864_set_line(LCD_CS1); mt12864_set_line(LCD_CS2); }

#define mt12864_backlight_on()    mt12864_clear_line(LCD_BACKLIGHT_PIN)
#define mt12864_backlight_off()   mt12864_set_line(LCD_BACKLIGHT)
#define is_mt12864_backlight_on() mt12864_is_line_set(LCD_BACKLIGHT_PIN)


#define mt12864_configure_ports() do {\
  sbi(DDRC, LCD_E);\
  sbi(DDRC, LCD_RW);\
  sbi(DDRC, LCD_A0);\
  sbi(DDRC, LCD_CS2);\
  sbi(DDRC, LCD_CS1);\
  sbi(DDRC, LCD_RES);\
  sbi(DDRC, LCD_BACKLIGHT);\
} while(0)

#define mt12864_clear_all_control_lines() do {\
  mt12864_clear_line (LCD_E);\
  mt12864_clear_line (LCD_RW);\
  mt12864_clear_line (LCD_A0);\
  mt12864_clear_line (LCD_CS2);\
  mt12864_clear_line (LCD_CS1);\
  mt12864_clear_line (LCD_RES);\
  mt12864_clear_line (LCD_BACKLIGHT);\
} while(0)

/*--------------------------------------------------------------------------------------------*/
/* LCD data bus is connected to Port B.                                                       */
/*--------------------------------------------------------------------------------------------*/
#define LCD_Data_Bus_to_Output()        DDRB = 0xff
#define LCD_Data_Bus_To_Input()         { DDRB = 0x00; PORTB = 0xff; }
#define Put_Data_to_LCD_Data_Bus(data)  PORTB = (data)
#define Get_Data_from_LCD_Data_Bus()    PINB



#endif

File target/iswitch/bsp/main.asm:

.EQU	DEBUG = 1

.INCLUDE	"m48def.inc"
.INCLUDE	"device.inc"

; TODO: init PRR (power reduction register)
; TODO: enable pull-ups on unused (floating) pins to minimize power consumption
; TODO: init and use watchdog
; TODO: power saving, sleep

; =========================================================================================
;
; HARDWARE:
;
; ATMEGA48
; 01		PD3/INT1/OC2B/PCINT19	O	Triac control 0
; 09		PD5/T1/OC0B/PCINT21		O	Triac control 1
; 11		PD7/AIN1/PCINT23		O	CAN Controller select (-CS)
; 23		PC0/ADC0/PCINT8			I	CAN Controller interrupt (-INT)
; 32		PD2/INT0/PCINT18		I	Zero cross interrupt
; =========================================================================================

.CSEG


; =========================================================================================
; Flash page 0 (ATMega48) - self-reprogrammable
; -----------------------------------------------------------------------------------------
.ORG		0	
.INCLUDE	"interrupt-table.asm"

; placed before RESET: so that any unexpected interrupt will cause reset
.INCLUDE	"empty-int-handlers.asm"
; -----------------------------------------------------------------------------------------
RESET:		; Main program start
; -----------------------------------------------------------------------------------------			
.INCLUDE	"wdt-init.asm"	; must be short enough to fit in the rest of the page!
; =========================================================================================



.ORG		32
; =========================================================================================
; CORE
; Flash pages 1+ (ATMega48) - not self-reprogrammable
; -----------------------------------------------------------------------------------------
.INCLUDE	"../../../shared/src/avrasm/core.asm"
; =========================================================================================




.ORG		1024
; =========================================================================================
; USER SECTION: Flash pages ?+ (ATMega48) - self-reprogrammable
; -----------------------------------------------------------------------------------------
.INCLUDE	"operations.inc"
.INCLUDE	"init.asm"
.INCLUDE	"timer1-driver.asm"
.INCLUDE	"keyboard-driver.asm"
.INCLUDE	"switch-handler.asm"
.INCLUDE	"user-can-message-dispatcher.asm"
.INCLUDE	"operations.asm"
; =========================================================================================





; =========================================================================================



.DSEG

.INCLUDE	"dimmer-control.inc"

.ORG		0x100	; TODO explain why 0x100
channel_0_data:		.byte 0x16
channel_1_data:		.byte 0x16

; =========================================================================================
.ESEG

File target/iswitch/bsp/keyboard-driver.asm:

; --------------------------------------------------------------------------------------
; debug **************
sUnrecognizedButton:
.db			"Unrecognized button!",13,10,0
sButtonToggled:
.db			"Button toggled",13,10,0
; debug **************

; invoked from TIM1_OVF when a signal noise (dribble) is suspended
read_keyboard:

			.def	current_buttons_state		= r23
			.def	previous_buttons_state		= r22
			.def	change_flags				= r22
			
			.equ	EVENT_DESC_ADDRESS_LOW		= 9
			.equ	EVENT_DESC_ADDRESS_HIGH		= 0
			.equ	EVENT_DESC_LENGTH			= 3		; 3 registers r9-r11, 3 bytes
			.def	channel						= r9
			.def	logical_button				= r10
			.def	action						= r11

			.def	current_control_register	= r2
			.def	temp						= r17

; --------------------------------------------------------------------------------------			

			in		current_buttons_state, BUTTONS_PORT		; read current buttons state from the port
			
.ifdef	DEBUG		; **********************************************************
			ldi		zl, low(sButtonToggled<<1)
			ldi		zh, high(sButtonToggled<<1)
			rcall	print

			mov		r1, previous_buttons_state
			rcall	printByteAsHex			

			mov		r1, current_buttons_state
			rcall	printByteAsHex						
.endif				; **********************************************************
			
			eor		change_flags, current_buttons_state		; what has changed?


.ifdef	DEBUG		; **********************************************************
			mov		r1, change_flags
			rcall	printByteAsHex			
			rcall	println			
.endif				; **********************************************************

			andi	change_flags, KEYBOARD_PORT_MASK
			brne	real_check
			ret

real_check:


			; the event detection code will identify the event with these 3 variables:

			; 'channel' contains the number of 'logical device' (pair of up+down buttons)
			; 'logical_button' contains 0 if 'up' button was toggled, 1 if 'down'
			; 'action' contains 0 if button was pressed, 1 if released

			; initial values are:
			clr		channel				; start with 'logical device' #0
			clr		logical_button				; start with 'up' button toggled
			clr		action						; start with 'pressed'


bh_check_button_up0:
			; check whether the UP0 button was toggled
			; ~~~~~~~~~~~~~~~~~~~~~~~~~~~~~~~~~~~~~~~~~~~~~
			sbrs	change_flags, PORTBIT_BUTTON_UP0			; skip if bit 4 is 1 (if UP0 was toggled => skip)
			rjmp	bh_check_button_down0						; go and check next button state
			; ~~~~~~~~~~~~~~~~~~~~~~~~~~~~~~~~~~~~~~~~~~~~~

			; Channel 0 UP button was toggled!
			; populate event variables appropriately
			; ~~~~~~~~~~~~~~~~~~~~~~~~~~~~~~~~~~~~~~~~~~~~~
			; up0 was toggled  => channel<-0, logical_button <- 0.
			; channel is already 0, logical_button is already 0 - nothing to do
			;
			; decide whether the button was pressed or released and populate 'action' appropriately			
			; bit =0? (pressed) => action=0 (pressed)
			; bit =1? (released) => action=1 (released)
			sbrc	current_buttons_state, PORTBIT_BUTTON_UP0	; skip next if bit=0 (pressed)
			inc		action										; execute this if bit=1 (released)
			; ~~~~~~~~~~~~~~~~~~~~~~~~~~~~~~~~~~~~~~~~~~~~~

			; event identified, now go and handle it
			; ~~~~~~~~~~~~~~~~~~~~~~~~~~~~~~~~~~~~~~~~~~~~~
			rjmp	handle_button_action								
			; ~~~~~~~~~~~~~~~~~~~~~~~~~~~~~~~~~~~~~~~~~~~~~


bh_check_button_down0:
			; check whether the DOWN0 button was toggled
			; ~~~~~~~~~~~~~~~~~~~~~~~~~~~~~~~~~~~~~~~~~~~~~
			sbrs	change_flags, PORTBIT_BUTTON_DOWN0			; skip if bit 6 is 1 (if DOWN0 was toggled => skip)
			rjmp	bh_check_button_up1
			; ~~~~~~~~~~~~~~~~~~~~~~~~~~~~~~~~~~~~~~~~~~~~~

			; Channel 0 DOWN button was toggled!
			; populate event variables appropriately
			; ~~~~~~~~~~~~~~~~~~~~~~~~~~~~~~~~~~~~~~~~~~~~~
			; down0 was toggled => channel<-0, logical_button<-1.
			; channel is already 0, logical_button is 0 => logical_button++
			inc		logical_button				; logical_button <- 1			
			;
			; decide whether the button was pressed or released and populate 'action' appropriately						sbrs	current_buttons_state, PORTBIT_BUTTON_UP0	; bit is 0? (pressed) => action=0 (pressed)
			sbrc	current_buttons_state, PORTBIT_BUTTON_DOWN0
			inc		action										
			; ~~~~~~~~~~~~~~~~~~~~~~~~~~~~~~~~~~~~~~~~~~~~~

			; event identified, now go and handle it
			; ~~~~~~~~~~~~~~~~~~~~~~~~~~~~~~~~~~~~~~~~~~~~~
			rjmp	handle_button_action
			; ~~~~~~~~~~~~~~~~~~~~~~~~~~~~~~~~~~~~~~~~~~~~~


bh_check_button_up1:
			inc		channel								; channel <- 1

			; check whether the UP1 button was toggled
			; ~~~~~~~~~~~~~~~~~~~~~~~~~~~~~~~~~~~~~~~~~~~~~
			sbrs	change_flags, PORTBIT_BUTTON_UP1			; skip if bit 4 is 1 (if UP1 was toggled => skip)
			rjmp	bh_check_button_down1
			; ~~~~~~~~~~~~~~~~~~~~~~~~~~~~~~~~~~~~~~~~~~~~~

			; Channel 1 UP button was toggled!
			; populate event variables appropriately
			; ~~~~~~~~~~~~~~~~~~~~~~~~~~~~~~~~~~~~~~~~~~~~~
			; up1 was toggled => channel <- 1, logical_button<-0.
			; channel is already 1, logical_button is already 0
			;
			; decide whether the button was pressed or released and populate 'action' appropriately
			sbrc	current_buttons_state, PORTBIT_BUTTON_UP1
			inc		action
			; ~~~~~~~~~~~~~~~~~~~~~~~~~~~~~~~~~~~~~~~~~~~~~
			
			; event identified, now go and handle it
			; ~~~~~~~~~~~~~~~~~~~~~~~~~~~~~~~~~~~~~~~~~~~~~
			rjmp	handle_button_action
			; ~~~~~~~~~~~~~~~~~~~~~~~~~~~~~~~~~~~~~~~~~~~~~


bh_check_button_down1:
			; check whether the DOWN1 button was toggled
			; ~~~~~~~~~~~~~~~~~~~~~~~~~~~~~~~~~~~~~~~~~~~~~
			sbrs	change_flags, PORTBIT_BUTTON_DOWN1		; skip if bit 6 is 1 (if DOWN1 was toggled => skip)
			rjmp	bh_glitch

			; Channel 1 DOWN button was toggled!
			; populate event variables appropriately
			; ~~~~~~~~~~~~~~~~~~~~~~~~~~~~~~~~~~~~~~~~~~~~~
			; down1 was toggled => channel <- 1, logical_button<-1.
			; channel is already 1, logical_button is 0 => logical_button++
			inc		logical_button
			;
			; decide whether the button was pressed or released and populate 'action' appropriately			
			sbrc	current_buttons_state, PORTBIT_BUTTON_DOWN1
			inc		action
			; ~~~~~~~~~~~~~~~~~~~~~~~~~~~~~~~~~~~~~~~~~~~~~
			
			; event identified, now go and handle it
			; ~~~~~~~~~~~~~~~~~~~~~~~~~~~~~~~~~~~~~~~~~~~~~
			rjmp	handle_button_action
			; ~~~~~~~~~~~~~~~~~~~~~~~~~~~~~~~~~~~~~~~~~~~~~


bh_glitch:	; we end up here if we could not identify any known event; should not happen!
			; ~~~~~~~~~~~~~~~~~~~~~~~~~~~~~~~~~~~~~~~~~~~~~

.ifdef	DEBUG
			; debug **************
			;ldi		zl, low(sUnrecognizedButton<<1)
			;ldi		zh, high(sUnrecognizedButton<<1)
			;rcall	print
			; debug **************
.endif
			
			; just in case, fill previous_buttons_state with "nothing was pressed"
			; previous_buttons_state <- 0xFF			
			eor		previous_buttons_state,	previous_buttons_state
			dec		previous_buttons_state
			ret	; nothing more to do
			; ~~~~~~~~~~~~~~~~~~~~~~~~~~~~~~~~~~~~~~~~~~~~~


; =============================================================================
PINCHINT2:

; Handler for button interrupts (PCINT2)

; 4 buttons are connected to the port D
; Any change on these pins results in the interrupt PINCHINT2 (PCINT16-23 correspond to PINCHINT2)

; pin 02	PD4/T0/XCK/PCINT20		I	Button UP0
; pin 10	PD6/AIN0/OC0A/PCINT22	I	Button DOWN0
; pin 30	PD0/RXD/PCINT16			I	Button UP1
; pin 31	PD1/TXD/PCINT17			I	Button DOWN1

; Keyboard states:
; -----------------------------------------------------------------------------
.equ	STATE_JUST_TOGGLED			= 3
; reaction: disable iterrupts, after 1 tick switch to state STATE_TOGGLED_1_TICK_AGO
.equ	STATE_TOGGLED_1_TICK_AGO	= 2
; 2 = 1 timer tick occurred. tick=>shift to state 1
.equ	STATE_TOGGLED_2_TICKS_AGO	= 1
; 1 = 2 timer tick occurred. enable keyboard interrupts, read kb, shift to state 0
.equ	STATE_TOGGLED_LONG_AGO		= 0
; 0 = > 2 timer tick occurred. do not do anything.
; -----------------------------------------------------------------------------
.def	keyboard_state				= r19

; =============================================================================
			


			; disable interrupts from keyboard
			; (will be re-enabled when dribble interval expires)
			ldi		r16, 0
			sts		BUTTONS_PCMSK, r16
			
.ifdef	DEBUG
			ldi		r16, '#'
			mov		r0, r16
			rcall	printChar
.endif


			; this state will make TIMER1 OVF handler to do some real job
			ldi		keyboard_state, STATE_JUST_TOGGLED
			
			reti
